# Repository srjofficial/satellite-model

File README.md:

# 🛰️ CubeSat-Style 1U Satellite Working Model

A comprehensive, fully open-source **1U CubeSat educational demonstrator (100 mm cube)** featuring autonomous dual-axis solar tracking, an ESP32-CAM imaging payload, environmental & electrical telemetry, and long-range LoRa packet downlink with automated ground station reassembly.

---

## 🖼️ 3D Model & PCB Previews

| 🛰️ 3D CAD Assembly (OpenSCAD / WebGL) | 🟢 Carrier PCB & Gerber Layout |
|:---:|:---:|
|  |  |
| *100 mm 1U chassis with pan/tilt solar tracker & camera aperture* | *90 × 86 mm 2-layer PCB layout with routed traces, ENIG pads & silkscreen* |

* 🌐 **Interactive 3D Web Viewer:** Open [`cad/view_model.html`](cad/view_model.html) in your browser for full 3D Orbit controls, real-time Pan/Tilt servo simulation, and an **Exploded View**!
* 📦 **PCB Fabrication Files:** Download [`hardware/gerbers.zip`](hardware/gerbers.zip) for instant manufacturing (JLCPCB, PCBWay, OSHPark).
* 🧪 **Proteus Integration:** Tango netlist and simulation guide available in [`hardware/proteus/`](hardware/proteus/).

```powershell
# Open interactive 3D model viewer in your browser
Start-Process "cad\view_model.html"
```

---

## 🚀 Key Features

* **☀️ Autonomous Dual-Axis Solar Tracking:** 4-quadrant LDR contrast bridge driving two SG90/MG90S servos across pan (10°–170°) and tilt (20°–160°) axes with software deadband and smooth 1° increments.
* **📸 Chunked LoRa Imaging Payload:** AI-Thinker ESP32-CAM captures QQVGA (160×120) JPEG stills, slices them into 200-byte packets protected by CRC-16/CCITT-FALSE checksums, and transmits over SX1278 LoRa.
* **⚡ Comprehensive Telemetry Suite:** Dual INA219 sensors (solar generation V/mA and battery charge/discharge V/mA), Bosch BME280 (temperature, atmospheric pressure, relative humidity), and MPU6050 6-DOF IMU (real-time pitch/roll attitude).
* **🔋 Power Management & Duty Cycling:** Single 18650 Li-ion battery charged via TP4056 with DW01 low-voltage protection, 5V boost converter, dedicated 3.3V LDO, and deep-sleep duty cycling on the camera payload.
* **📡 Ground Station & Python Reassembly:** ESP32 + SX1278 receiver firmware that validates hardware & software CRC-16 checksums, paired with a Python application that reconstructs JPEG images and logs synchronized telemetry to CSV.
* **🛠️ Parametric CAD & Carrier PCB:** Parametric OpenSCAD design (`cad/satellite.scad`) matched to a custom 90×86 mm 2-layer KiCad carrier PCB (`hardware/kicad/`) with ground pours, M3 standoffs, and antenna keep-out zones.

---

## 🏗️ System Architecture

```mermaid
flowchart TD
  subgraph EPS["Electrical Power Subsystem (EPS)"]
    SP["☀️ Solar Panel (Max 6V)"] --> J7["INA219 #1 (Solar V & mA)"]
    J7 --> CH["TP4056 Charger + DW01 Protection"]
    CH <--> J9["INA219 #2 (Battery V & +/-mA)"]
    J9 <--> BAT["🔋 18650 Li-ion Cell (3.7V)"]
    CH --> SW["Power Switch"]
    SW --> BST["⚡ 5V Boost Converter"]
    BST --> RAIL5["+5V Power Rail"]
    RAIL5 --> LDO["AMS1117-3.3 LDO"]
    LDO --> RAIL3["+3.3V Power Rail"]
  end

  subgraph OAS["OBC & Attitude Subsystem (Tracker)"]
    RAIL5 --> TRK["ESP32 DevKit 30-Pin"]
    LDR["4x LDR Quadrant Bridge"] --> TRK
    BME["BME280 (Temp/Press/Hum)"] -->|"I2C (0x76)"| TRK
    MPU["MPU6050 (Pitch/Roll)"] -->|"I2C (0x68)"| TRK
    J7 -->|"I2C (0x40)"| TRK
    J9 -->|"I2C (0x41)"| TRK
    TRK -->|"PWM GPIO 18"| SRV1["Pan Servo (10°-170°)"]
    TRK -->|"PWM GPIO 19"| SRV2["Tilt Servo (20°-160°)"]
  end

  subgraph PAYLOAD["Camera Payload & Communications"]
    RAIL5 --> CAM["AI-Thinker ESP32-CAM"]
    RAIL3 --> LORA["SX1278 LoRa Module (433 MHz)"]
    TRK -->|"UART2 115200 (GPIO 17 to GPIO 3)"| CAM
    CAM -->|"HSPI (SCK 14, MISO 12, MOSI 13, NSS 15)"| LORA
  end

  subgraph GROUND["Ground Segment"]
    LORA -.->|"LoRa RF 433 MHz (SF7, BW 125kHz)"| GS_RF["Ground SX1278"]
    GS_RF --> GS_MCU["Ground ESP32 DevKit"]
    GS_MCU -->|"USB Serial (PKT, hex, rssi, snr)"| PY["Python Ground Station App"]
    PY --> CSV["📊 telemetry.csv"]
    PY --> JPG["🖼️ Reassembled JPEGs"]
  end
```

---

## 📦 Downlink Protocol & Packet Format

Telemetry and image chunks are packed into byte frames protected by **CRC-16/CCITT-FALSE** (`poly=0x1021`, `init=0xFFFF`):

| Offset (Bytes) | Field | Description |
|:---:|:---|:---|
| `0` | **Type** | `0x10` = Image Chunk, `0x20` = Telemetry |
| `1` | **Image ID** | Sequential image session ID (0–255, wraps) |
| `2..3` | **Sequence No** | 16-bit big-endian chunk index (0-based) |
| `4..5` | **Total Packets** | 16-bit big-endian total chunk count for image |
| `6` | **Length ($N$)** | Payload length ($\le 200$ bytes) |
| `7 .. 6+N` | **Payload** | Raw JPEG chunk or ASCII CSV telemetry string |
| `7+N .. 8+N` | **CRC-16** | CRC-16/CCITT calculated over bytes `0` through `6+N` |

### Telemetry String Structure
Transmitted over UART from the Tracker MCU to the Camera payload once per second:
```csv
T,solarV,solar_mA,battV,batt_mA,tempC,pressHPa,humPct,pitch,roll,pan,tilt
```

---

## 🗂️ Repository Structure

```
satellite-model/
├── cad/
│   ├── satellite.scad          # Parametric OpenSCAD 1U cube model
│   ├── view_model.html         # Interactive WebGL 3D model viewer
│   └── README.md               # 3D export instructions (STL/STEP)
├── firmware/
│   ├── esp32-cam-node/         # Camera payload, packetizer, LoRa TX, sleep
│   ├── solar-tracker/          # 4-quadrant LDR tracking, I2C sensors, servos
│   └── ground-station/         # ESP32 + LoRa receiver with CRC verification
├── ground-station-ui/
│   ├── ground_station.py       # Python image reassembly & CSV telemetry logger
│   └── requirements.txt        # Python dependencies (pyserial)
├── hardware/
│   ├── bom.csv                 # Detailed Bill of Materials
│   ├── netlist.csv             # Complete pin-to-pin electrical netlist
│   ├── pinmap.md               # Pin assignment documentation
│   └── kicad/
│       ├── generate_kicad.py   # Algorithmic router & KiCad project generator
│       ├── satellite.kicad_sch # Carrier board schematic
│       ├── satellite.kicad_pcb # Routed 2-layer PCB (90x86 mm)
│       ├── satellite.kicad_pro # KiCad 8 project configuration
│       ├── satellite.pretty/   # Custom footprints
│       └── pcb-preview.png     # Rendered PCB preview
└── docs/
    ├── architecture.md         # Subsystem dataflow & packet specification
    ├── power-budget.md         # Power consumption estimates & duty cycle formula
    ├── test-results.md         # Test result template
    └── linkedin-post.md        # Summary post template
```

---

## 🔧 Bill of Materials (BOM)

| Ref | Component | Description | Qty |
|---|---|---|:---:|
| **U1 / J1** | AI-Thinker ESP32-CAM | Camera payload node (OV2640) | 1 |
| **U2 / J2** | ESP32 DevKit (30-pin) | Solar tracker & telemetry aggregator | 1 |
| **U3 / J3** | SX1278 Ra-02 (433 MHz) | LoRa transceiver module (satellite node) | 1 |
| **U4** | SX1278 Ra-02 + ESP32 | Ground station receiver node | 1 |
| **SEN1 / J7** | INA219 Breakout | Solar current & voltage monitor (`0x40`) | 1 |
| **SEN2 / J9** | INA219 Breakout | Battery current & voltage monitor (`0x41`, solder A0) | 1 |
| **SEN3 / J14**| BME280 Breakout | Temperature, pressure, humidity (`0x76`) | 1 |
| **SEN4 / J15**| MPU6050 Breakout | 6-DOF Gyro & Accelerometer (`0x68`) | 1 |
| **ACT1, ACT2**| SG90 or MG90S | Pan & Tilt servos | 2 |
| **PWR1 / J8** | TP4056 Module | Li-ion charger with DW01 protection | 1 |
| **PWR2 / J12**| MT3608 Boost Module | 3.7V to 5.0V step-up DC-DC converter | 1 |
| **PWR3 / J13**| AMS1117-3.3 Module | 5.0V to 3.3V dedicated LDO | 1 |
| **BAT / J10** | 18650 Li-ion Cell | 3.7V nominal, 2000–3000 mAh + holder | 1 |
| **PV / J6**   | Mini Solar Panel | $\le 6\text{ V}$ open circuit (50–150 mA) | 1 |
| **LDR1–4**    | GL5528 LDR + 10k 0805 | Quadrant light detection dividers | 4 |
| **C1, C2**    | 470 µF 10V Radial | 5V rail bulk capacitors for servo surge absorption | 2 |

---

## ⚡ Setup & Flashing Instructions

### 1. Arduino IDE Setup
Install the **ESP32 Board Package** in Arduino IDE and install the following libraries via the Library Manager:
* `LoRa` (by Sandeep Mistry)
* `ESP32Servo` (by Kevin Harrington)
* `Adafruit INA219`
* `Adafruit BME280 Library`
* `Adafruit MPU6050`
* `Adafruit Unified Sensor`

### 2. Flashing the Tracker Node
1. Open [`firmware/solar-tracker/solar-tracker.ino`](firmware/solar-tracker/solar-tracker.ino).
2. Board: **ESP32 Dev Module** (30-pin DevKit).
3. Connect USB and click **Upload**.

### 3. Flashing the ESP32-CAM Node
> ⚠️ **IMPORTANT:** Disconnect the tracker telemetry line (`ESP32-CAM RX / GPIO 3`) and short `GPIO 0` to `GND` before powering on to enter flashing mode.
1. Open [`firmware/esp32-cam-node/esp32-cam-node.ino`](firmware/esp32-cam-node/esp32-cam-node.ino).
2. Board: **AI Thinker ESP32-CAM**.
3. Upload using an external USB-to-UART adapter (5V, GND, U0TXD, U0RXD).
4. Remove the `GPIO 0` to `GND` jumper and reconnect the telemetry wire after flashing.

### 4. Flashing the Ground Station
1. Open [`firmware/ground-station/ground-station.ino`](firmware/ground-station/ground-station.ino).
2. Connect the ground station ESP32 and click **Upload**.

### 5. Running the Ground Station App
```bash
# Navigate to the ground station directory
cd ground-station-ui

# Install dependencies
pip install -r requirements.txt

# Run the receiver (replace COM5 with your port, or /dev/ttyUSB0 on Linux/macOS)
python ground_station.py --port COM5
```
* **Telemetries:** Appended in real-time to `received/telemetry.csv` with timestamps, signal RSSI, and SNR.
* **Images:** Fully reassembled JPEGs saved automatically to `received/img_<id>_<timestamp>.jpg`.

---

## 📊 Power Budget & Battery Life

| Subsystem / Component | State | Current @ 5V / 3.3V |
|---|---|:---:|
| **ESP32 DevKit (Tracker)** | Active (Tracking & Reading Sensors) | ~50–70 mA |
| **Dual Servos (SG90/MG90S)**| Moving / Idle | ~150–500 mA (peak) / ~10 mA |
| **Sensors (INA219 x2, BME280, MPU6050)** | Active I2C | ~5 mA |
| **ESP32-CAM (Payload)** | Capture & LoRa TX (~5–8s burst) | ~200–280 mA |
| **ESP32-CAM (Payload)** | Deep Sleep (Duty cycle between shots) | ~6–8 mA |

* **Duty Cycle Formula:**
  $$I_{\text{avg}} = \frac{I_{\text{active}} \cdot t_{\text{active}} + I_{\text{sleep}} \cdot t_{\text{sleep}}}{t_{\text{active}} + t_{\text{sleep}}}$$
* With an average consumption of ~120 mA and a single 2500 mAh 18650 cell, expected continuous operation without sunlight is **16–20+ hours**, extended indefinitely under active solar tracking.

---

## 📜 License

This project is open-source under the [MIT License](LICENSE).
Feel free to use it for academic, research, or personal educational projects!

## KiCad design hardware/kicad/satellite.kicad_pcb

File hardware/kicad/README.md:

# KiCad project (carrier board, rev A)

Open `satellite.kicad_pro` in **KiCad 8 or newer**.

| File | Contents |
|---|---|
| `satellite.kicad_sch` | Schematic: every module as a header symbol, nets joined by labels |
| `satellite.kicad_pcb` | 90 x 86 mm 2-layer board, placed and routed, GND pour on both layers, antenna keep-out |
| `satellite.pretty/` | Footprints (headers, module sockets, 0805, radial cap, test point, M3 hole) |
| `generate_kicad.py` | Regenerates everything above and `../netlist.csv` (`python3 generate_kicad.py`) |
| `pcb-preview.png` | Picture of the routed board |

## How the board works
Nothing is soldered directly to the board except headers and small passives. Modules (ESP32-CAM, ESP32 DevKit, Ra-02 LoRa, TP4056, boost, LDO, INA219 x2, BME280, MPU6050) plug into or wire to headers. Servos, LDRs, solar panel, battery holder and switch connect through 2-3 pin headers.

Mounting holes: M3 at 80 x 76 mm spacing (matches `cad/satellite.scad`). The top edge (y = 0) is the camera edge.

## First steps in KiCad
1. Open the PCB, press **B** to fill zones, then run **Inspect > Design Rules Checker**.
2. Open the schematic, run **Inspect > Electrical Rules Checker**. Expect warnings about passive pins; every pin is typed "passive" on purpose.
3. **Tools > Update PCB from Schematic** should report no changes.
4. Check the 3D viewer, then **File > Fabrication Outputs > Gerbers/Drill** and save to `gerbers/`.

## What was and was not checked
Checked by script: file syntax (balanced S-expressions), every schematic label sits on a pin, all 24 signal/power nets routed, minimum copper clearance 0.216 mm against a 0.2 mm rule, nothing inside the antenna keep-out or near the edge.

**Not checked:** I could not open these files in KiCad itself. Expect small load or DRC surprises. Fix them in KiCad rather than re-running the script if you have already edited the board.

## Verify before ordering a board
- **Module pinouts vary by clone.** Compare the ESP32-CAM, DevKit, Ra-02, INA219 and TP4056 pin order and row spacing against your actual modules. Row spacing is set in `generate_kicad.py` (`ROW_CAM`, `ROW_DEV`); edit and re-run.
- Servo and boost traces are 0.8 mm; signals 0.4 mm. Servo stall current can exceed what one 18650 through a boost converter delivers. Keep the 470 uF capacitors.
- The battery path goes through INA219 #2 (0.1 ohm shunt), so peak load current drops roughly 0.1 V per amp.
- GPIO12 (LoRa MISO) is an ESP32 boot-strap pin and GPIO2 (LoRa RESET) must be low or floating to flash; unplug the LoRa module if flashing fails.
- Label the board "untested design" until built and tested.

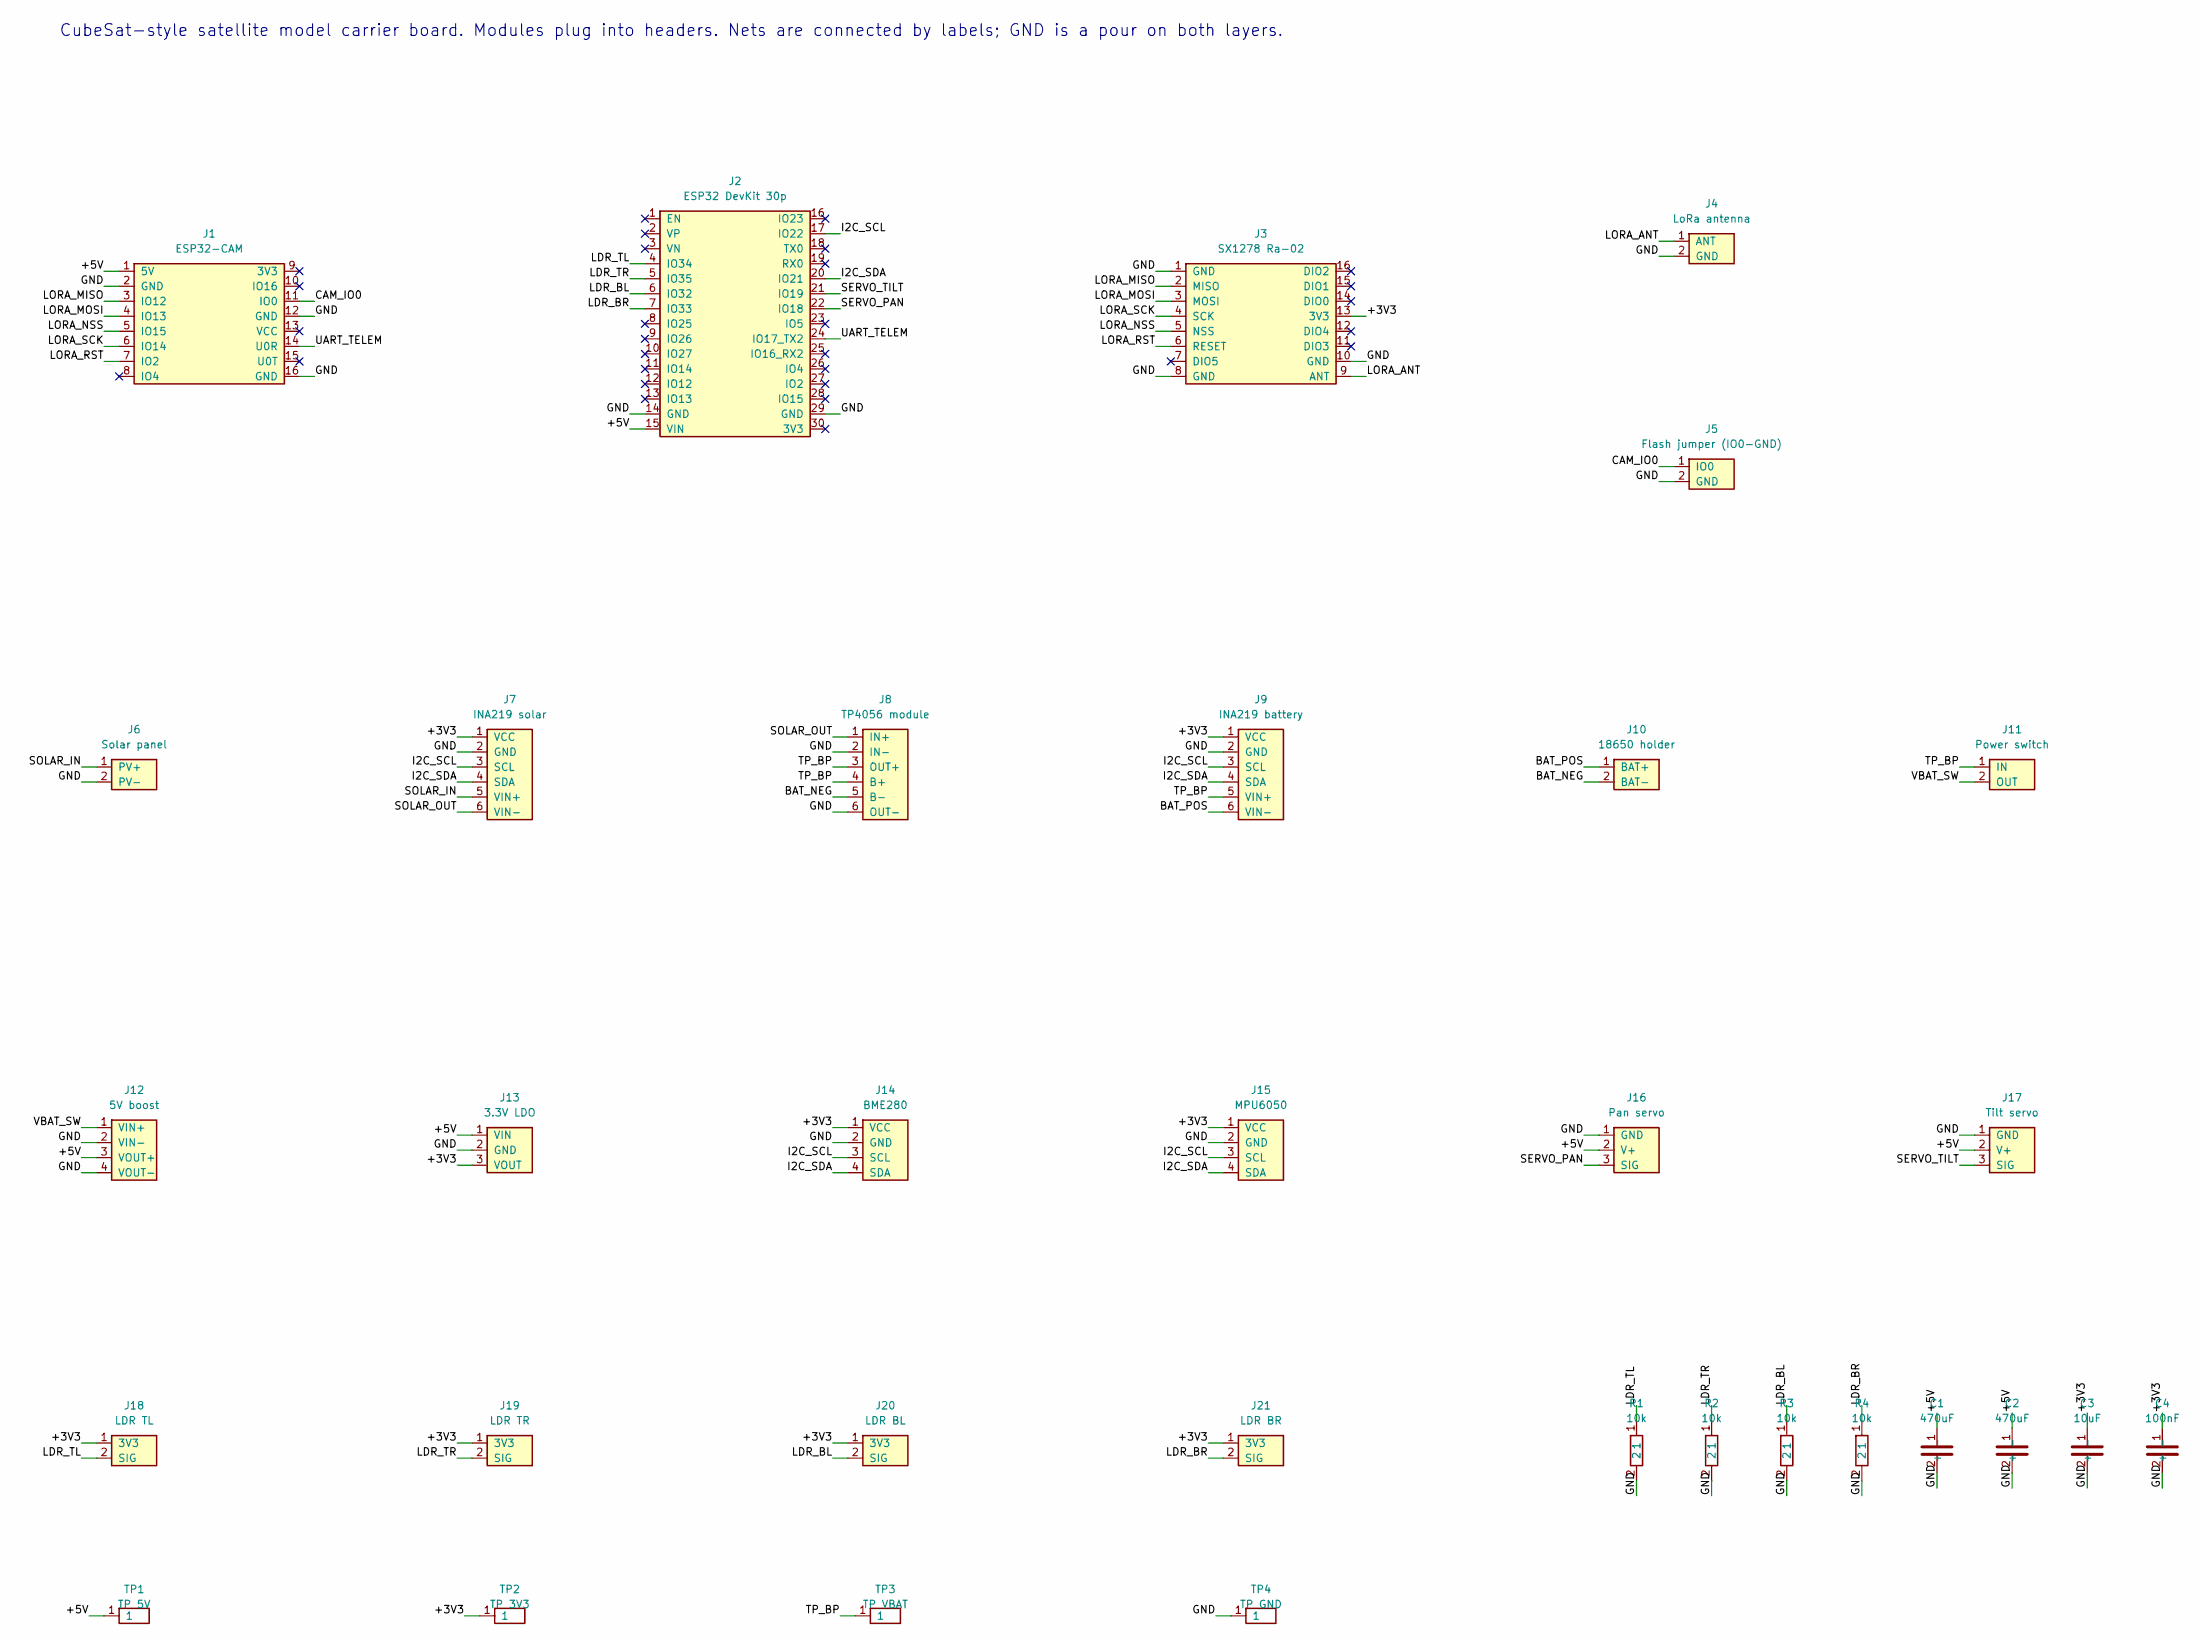
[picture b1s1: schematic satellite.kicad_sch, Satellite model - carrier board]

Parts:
C1, C2: 470uF; CP_Radial_D8.0mm_P3.50mm
C3: 10uF; C_0805
C4: 100nF; C_0805
J1: ESP32-CAM; ESP32-CAM_Socket_2x08_Row22.86mm
J2: ESP32 DevKit 30p; ESP32_DevKit_30pin_Socket_Row22.86mm
J3: SX1278 Ra-02; SX1278_RA-02_2x08_P2.00mm_Row16mm
J4: LoRa antenna; Header_1x02_P2.54mm_XAxis
J5: Flash jumper (IO0-GND); Header_1x02_P2.54mm_XAxis
J6: Solar panel; Header_1x02_P2.54mm_XAxis
J7: INA219 solar; Header_1x06_P2.54mm_XAxis
J8: TP4056 module; Header_1x06_P2.54mm_XAxis
J9: INA219 battery; Header_1x06_P2.54mm_XAxis
J10: 18650 holder; Header_1x02_P2.54mm_XAxis
J11: Power switch; Header_1x02_P2.54mm_XAxis
J12: 5V boost; Header_1x04_P2.54mm_XAxis
J13: 3.3V LDO; Header_1x03_P2.54mm_XAxis
J14: BME280; Header_1x04_P2.54mm_XAxis
J15: MPU6050; Header_1x04_P2.54mm_XAxis
J16: Pan servo; Header_1x03_P2.54mm_XAxis
J17: Tilt servo; Header_1x03_P2.54mm_XAxis
J18: LDR TL; Header_1x02_P2.54mm_XAxis
J19: LDR TR; Header_1x02_P2.54mm_XAxis
J20: LDR BL; Header_1x02_P2.54mm_XAxis
J21: LDR BR; Header_1x02_P2.54mm_XAxis
R1, R2, R3, R4: 10k; R_0805
TP1: TP 5V; TestPoint_Pad_D2.0mm
TP2: TP 3V3; TestPoint_Pad_D2.0mm
TP3: TP VBAT; TestPoint_Pad_D2.0mm
TP4: TP GND; TestPoint_Pad_D2.0mm

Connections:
+3V3: C3.1, C4.1, J3.13 (3V3), J7.1 (VCC), J9.1 (VCC), J13.3 (VOUT), J14.1 (VCC), J15.1 (VCC), J18.1 (3V3), J19.1 (3V3), J20.1 (3V3), J21.1 (3V3), TP2.1
+5V: C1.1 (+), C2.1 (+), J1.1 (5V), J2.15 (VIN), J12.3 (VOUT+), J13.1 (VIN), J16.2 (V+), J17.2 (V+), TP1.1
BAT_NEG: J8.5 (B-), J10.2 (BAT-)
BAT_POS: J9.6 (VIN-), J10.1 (BAT+)
CAM_IO0: J1.11 (IO0), J5.1 (IO0)
GND: C1.2 (-), C2.2 (-), C3.2, C4.2, J1.2 (GND), J1.12 (GND), J1.16 (GND), J2.14 (GND), J2.29 (GND), J3.1 (GND), J3.8 (GND), J3.10 (GND), J4.2 (GND), J5.2 (GND), J6.2 (PV-), J7.2 (GND), J8.2 (IN-), J8.6 (OUT-), J9.2 (GND), J12.2 (VIN-), J12.4 (VOUT-), J13.2 (GND), J14.2 (GND), J15.2 (GND), J16.1 (GND), J17.1 (GND), R1.2, R2.2, R3.2, R4.2, TP4.1
I2C_SCL: J2.17 (IO22), J7.3 (SCL), J9.3 (SCL), J14.3 (SCL), J15.3 (SCL)
I2C_SDA: J2.20 (IO21), J7.4 (SDA), J9.4 (SDA), J14.4 (SDA), J15.4 (SDA)
LDR_BL: J2.6 (IO32), J20.2 (SIG), R3.1
LDR_BR: J2.7 (IO33), J21.2 (SIG), R4.1
LDR_TL: J2.4 (IO34), J18.2 (SIG), R1.1
LDR_TR: J2.5 (IO35), J19.2 (SIG), R2.1
LORA_ANT: J3.9 (ANT), J4.1 (ANT)
LORA_MISO: J1.3 (IO12), J3.2 (MISO)
LORA_MOSI: J1.4 (IO13), J3.3 (MOSI)
LORA_NSS: J1.5 (IO15), J3.5 (NSS)
LORA_RST: J1.7 (IO2), J3.6 (RESET)
LORA_SCK: J1.6 (IO14), J3.4 (SCK)
SERVO_PAN: J2.22 (IO18), J16.3 (SIG)
SERVO_TILT: J2.21 (IO19), J17.3 (SIG)
SOLAR_IN: J6.1 (PV+), J7.5 (VIN+)
SOLAR_OUT: J7.6 (VIN-), J8.1 (IN+)
TP_BP: J8.3 (OUT+), J8.4 (B+), J9.5 (VIN+), J11.1 (IN), TP3.1
UART_TELEM: J1.14 (U0R), J2.24 (IO17_TX2)
VBAT_SW: J11.2 (OUT), J12.1 (VIN+)

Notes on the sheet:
CubeSat-style satellite model carrier board. Modules plug into headers. Nets are connected by labels; GND is a pour on both layers.

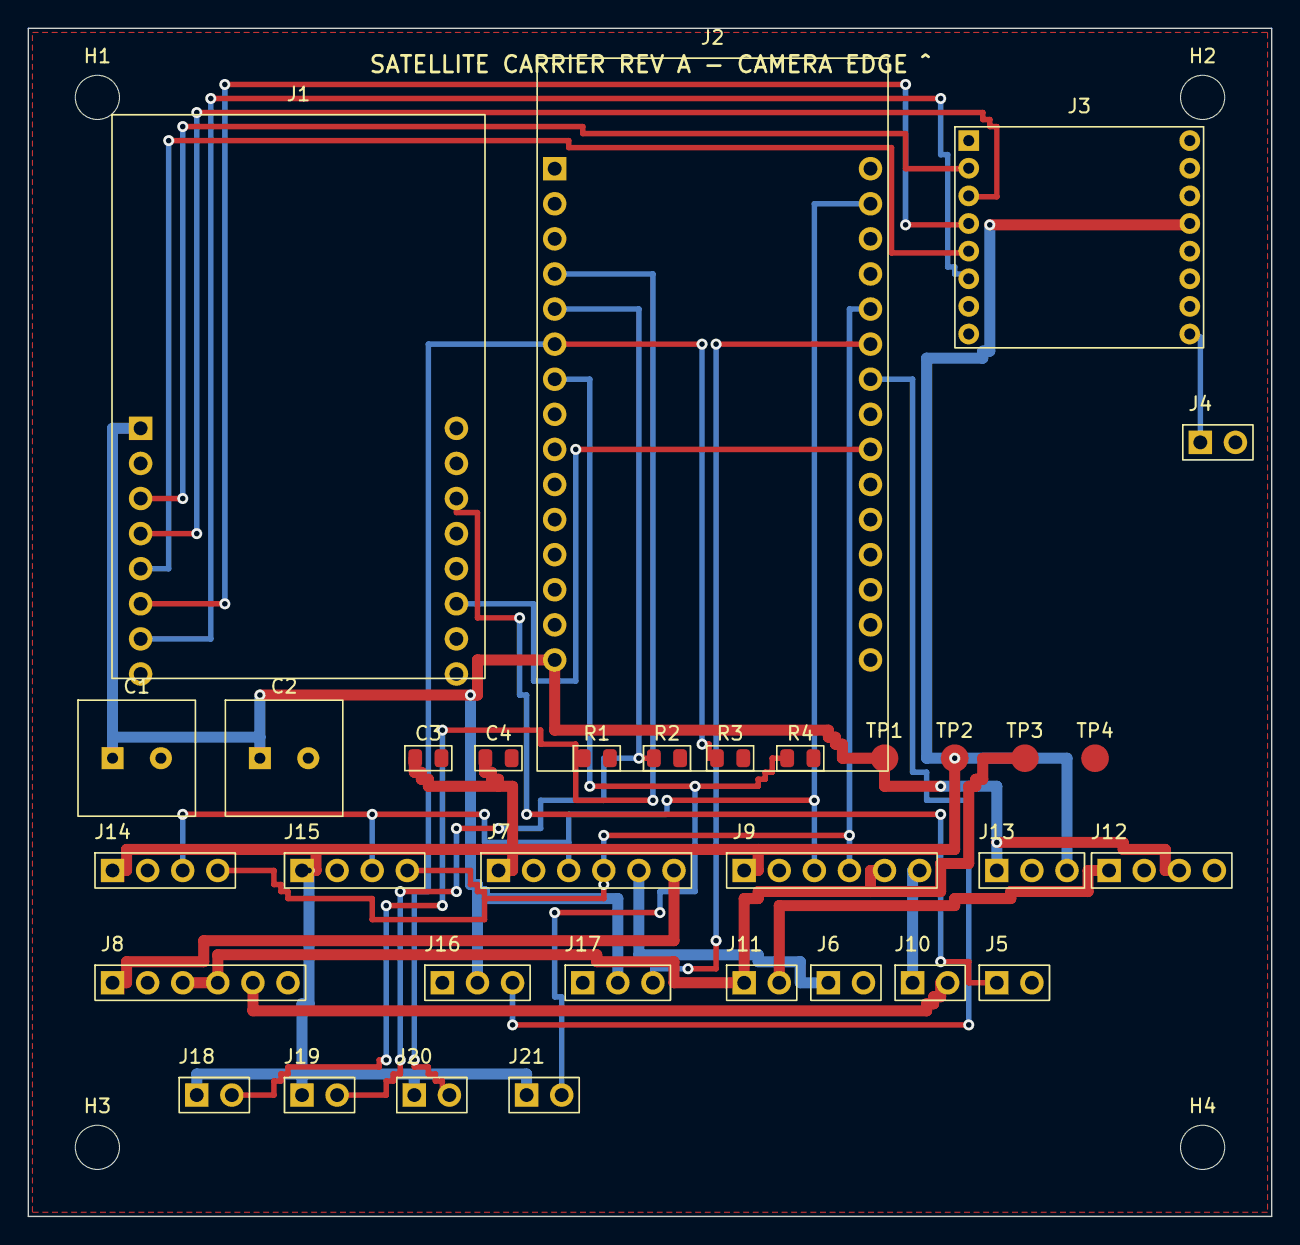
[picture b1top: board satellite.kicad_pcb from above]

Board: 2 copper layers, 90.0 x 86.0 mm, 37 parts (0 on the bottom side), 25 nets.

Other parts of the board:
H1, H2, H3, H4: M3; MountingHole_3.2mm_M3

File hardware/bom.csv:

ref,part,qty,notes
J1,AI-Thinker ESP32-CAM + 2x 1x8 female header,1,camera node
J2,ESP32 DevKit 30-pin + 2x 1x15 female header,1,tracker/telemetry; check row spacing
J3,SX1278 Ra-02 433 MHz module,1,solder to board or use 2.0 mm adapter; second one for ground station
J4,1x2 pin header,1,LoRa antenna pigtail / wire
J5 J6 J10 J11,1x2 pin header,4,flash jumper / solar / battery holder / switch
J7 J9,INA219 breakout + 1x6 header,2,set second to 0x41 (solder A0)
J8,TP4056 module with DW01 protection + 1x6 header,1,
J12,5V boost module (MT3608 or similar) + 1x4 header,1,set 5.0 V before connecting
J13,3.3V LDO module (AMS1117-3.3) + 1x3 header,1,
J14 J15,BME280 and MPU6050 breakouts + 1x4 header,2,BME280 address 0x76
J16 J17,SG90 or MG90S servo + 1x3 header,2,pan / tilt
J18-J21,LDR (GL5528 or similar) + 1x2 header,4,quadrant sun sensor
R1-R4,10k 0805 resistor,4,LDR dividers
C1 C2,470 uF 10 V radial 8 mm,2,5 V bulk
C3,10 uF 0805,1,3.3 V
C4,100 nF 0805,1,3.3 V
TP1-TP4,Test pad 2 mm,4,+5V / +3V3 / VBAT / GND
H1-H4,M3 screw + 6 mm standoff,4,
PV1,Solar panel 5-6V small,1,open-circuit voltage must stay <= 6 V
BT1,18650 cell + holder,1,protected cell recommended
ANT1,433 MHz antenna,2,one per LoRa module
-,3D-printed frame (PLA/PETG),1,see cad/

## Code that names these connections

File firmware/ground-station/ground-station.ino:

// Ground station: ESP32 DevKit + SX1278. Verifies CRC and forwards packets over USB serial.
// Output line: PKT,<hex>,<rssi>,<snr>
#include <SPI.h>
#include <LoRa.h>

#define LORA_FREQ 433E6
#define LORA_SF   7
#define LORA_BW   125E3
#define LORA_SCK  18
#define LORA_MISO 19
#define LORA_MOSI 23
#define LORA_SS   5
#define LORA_RST  14
#define LORA_DIO0 26

uint16_t crc16(const uint8_t *d, size_t n) {
  uint16_t c = 0xFFFF;
  while (n--) {
    c ^= (uint16_t)(*d++) << 8;
    for (int i = 0; i < 8; i++) c = (c & 0x8000) ? (c << 1) ^ 0x1021 : (c << 1);
  }
  return c;
}

void setup() {
  Serial.begin(115200);
  SPI.begin(LORA_SCK, LORA_MISO, LORA_MOSI, LORA_SS);
  LoRa.setPins(LORA_SS, LORA_RST, LORA_DIO0);
  if (!LoRa.begin(LORA_FREQ)) { Serial.println("ERR,LoRa init failed"); while (1) delay(1000); }
  LoRa.setSpreadingFactor(LORA_SF);
  LoRa.setSignalBandwidth(LORA_BW);
  LoRa.setCodingRate4(5);
  LoRa.enableCrc();
  Serial.println("INFO,ground station ready");
}

void loop() {
  int sz = LoRa.parsePacket();
  if (sz < 9) return;
  uint8_t buf[256];
  int n = 0;
  while (LoRa.available() && n < 256) buf[n++] = LoRa.read();
  if (n < 9) return;
  uint16_t rx = (buf[n - 2] << 8) | buf[n - 1];
  if (crc16(buf, n - 2) != rx) { Serial.println("ERR,crc"); return; }
  Serial.print("PKT,");
  for (int i = 0; i < n; i++) { if (buf[i] < 16) Serial.print('0'); Serial.print(buf[i], HEX); }
  Serial.print(',');
  Serial.print(LoRa.packetRssi());
  Serial.print(',');
  Serial.println(LoRa.packetSnr());
}

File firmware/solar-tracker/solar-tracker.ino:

// Solar tracker + telemetry. Board: ESP32 DevKit (30-pin).
// Libraries: ESP32Servo, Adafruit INA219, Adafruit BME280, Adafruit MPU6050, Adafruit Unified Sensor.
#include <Wire.h>
#include <math.h>
#include <ESP32Servo.h>
#include <Adafruit_INA219.h>
#include <Adafruit_BME280.h>
#include <Adafruit_MPU6050.h>

// Pins
#define PIN_PAN   18
#define PIN_TILT  19
#define LDR_TL 34
#define LDR_TR 35
#define LDR_BL 32
#define LDR_BR 33
#define UART_TX2 17   // -> ESP32-CAM RX (GPIO3)
#define UART_RX2 16

// Tracking
#define DEADBAND   150     // ADC counts (0-4095)
#define STEP_DEG   1
#define PAN_MIN 10
#define PAN_MAX 170
#define TILT_MIN 20
#define TILT_MAX 160
#define LOOP_MS 100
#define TELEM_MS 1000

Servo pan, tilt;
int panA = 90, tiltA = 90;
Adafruit_INA219 inaSolar(0x40), inaBatt(0x41);   // solder A0 on the second board for 0x41
Adafruit_BME280 bme;
Adafruit_MPU6050 mpu;
bool okSolar, okBatt, okBme, okMpu;
uint32_t lastTelem = 0;

int readAvg(int pin) {
  long s = 0;
  for (int i = 0; i < 16; i++) s += analogRead(pin);
  return s / 16;
}

void setup() {
  Serial.begin(115200);
  Serial2.begin(115200, SERIAL_8N1, UART_RX2, UART_TX2);
  Wire.begin(21, 22);
  analogReadResolution(12);
  pan.setPeriodHertz(50);  tilt.setPeriodHertz(50);
  pan.attach(PIN_PAN, 500, 2400);
  tilt.attach(PIN_TILT, 500, 2400);
  pan.write(panA); tilt.write(tiltA);
  okSolar = inaSolar.begin();
  okBatt  = inaBatt.begin();
  okBme   = bme.begin(0x76);
  okMpu   = mpu.begin();
  Serial.println("INFO,Solar tracker booting...");
  Serial.printf("INFO,INA_Solar:%d INA_Batt:%d BME280:%d MPU6050:%d\n", okSolar, okBatt, okBme, okMpu);
}

void track() {
  int tl = readAvg(LDR_TL), tr = readAvg(LDR_TR), bl = readAvg(LDR_BL), br = readAvg(LDR_BR);
  int top = (tl + tr) / 2, bot = (bl + br) / 2;
  int left = (tl + bl) / 2, right = (tr + br) / 2;
  // Flip signs if your mechanics move the wrong way
  if (abs(top - bot) > DEADBAND)   tiltA += (top > bot) ? STEP_DEG : -STEP_DEG;
  if (abs(left - right) > DEADBAND) panA += (left > right) ? -STEP_DEG : STEP_DEG;
  panA = constrain(panA, PAN_MIN, PAN_MAX);
  tiltA = constrain(tiltA, TILT_MIN, TILT_MAX);
  pan.write(panA); tilt.write(tiltA);
}

void telemetry() {
  float sv = okSolar ? inaSolar.getBusVoltage_V() : 0, sm = okSolar ? inaSolar.getCurrent_mA() : 0;
  float bv = okBatt ? inaBatt.getBusVoltage_V() : 0,  bm = okBatt ? inaBatt.getCurrent_mA() : 0;
  float t = okBme ? bme.readTemperature() : 0, p = okBme ? bme.readPressure() / 100.0 : 0, h = okBme ? bme.readHumidity() : 0;
  float pitch = 0, roll = 0;
  if (okMpu) {
    sensors_event_t a, g, tmp;
    mpu.getEvent(&a, &g, &tmp);
    pitch = atan2(a.acceleration.x, sqrt(a.acceleration.y * a.acceleration.y + a.acceleration.z * a.acceleration.z)) * 57.2958;
    roll  = atan2(a.acceleration.y, a.acceleration.z) * 57.2958;
  }
  char line[160];
  snprintf(line, sizeof(line), "T,%.2f,%.0f,%.2f,%.0f,%.1f,%.1f,%.0f,%.0f,%.0f,%d,%d",
           sv, sm, bv, bm, t, p, h, pitch, roll, panA, tiltA);
  Serial2.println(line);
  Serial.println(line);
}

void loop() {
  track();
  if (millis() - lastTelem >= TELEM_MS) { lastTelem = millis(); telemetry(); }
  delay(LOOP_MS);
}

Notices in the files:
README.md:
License: MIT
